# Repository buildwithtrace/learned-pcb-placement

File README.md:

# learned-pcb-placement

GNN-guided simulated annealing for PCB component placement. We train a Graph Attention Network on SA rollout data to learn which components to move and where, then use these predictions to bias the SA search. Early results show up to 9.2% HPWL reduction on KiCad designs. Dataset includes production boards up to 681 components (Antmicro Jetson Orin baseboard, HackRF One SDR).

**Paper:** [adekoya2026_gat_pcb_placement.pdf](adekoya2026_gat_pcb_placement.pdf)

## Architecture

```
KiCad .kicad_pcb
     │
     ▼
┌──────────────┐
│  S-expr Parser │ ──→ Components, Nets, Board geometry
└──────┬───────┘
       │
       ▼
┌──────────────┐     ┌──────────────┐
│  Graph Laplacian │ ──→ │ Spectral Init │ (Fiedler vectors)
│  L = D - A       │     └──────┬───────┘
└──────────────┘              │
       │                      ▼
       ▼             ┌──────────────┐
┌──────────────┐     │   SA Rollouts  │ ──→ Training data
│  GAT (2-layer)  │◀──  │  10 × short SA │     (accepted moves,
│  4-head attn    │     └──────────────┘      improvements)
│  move + quality │
└──────┬───────┘
       │
       ▼
┌──────────────────────────┐
│  GNN-Guided SA              │
│  P(component i) ∝ softmax(q_i / τ)  │
│  Δx, Δy = GNN prediction + noise    │
│  Accept via Boltzmann: e^{-ΔE/T}    │
└──────────────────────────┘
       │
       ▼
   Optimized Placement
```

## Results

Evaluated on 12 KiCad PCBs (5 to 94 components) parsed directly from `.kicad_pcb` files, sourced from open-source hardware on GitHub. Three additional production boards (207 to 681 components) are included in the dataset for GPU/TPU evaluation via Colab.

| Board | Components | Nets | SA HPWL | GNN HPWL | HPWL Δ | SA Cost | GNN Cost |
|-------|-----------|------|---------|----------|--------|---------|----------|
| stickhub | 94 | 45 | 1125.9 | **1022.1** | **-9.2%** | 1127.8 | 1757.3 |
| rp2040_debugger | 69 | 55 | 1248.8 | 1375.4 | +10.1% | 1251.1 | 1464.6 |
| motor_controller | 51 | 36 | 883.2 | 918.4 | +4.0% | 883.5 | 1116.6 |
| keyboard_rev0 | 37 | 46 | 3086.2 | 4228.8 | +37.0% | 8459.2 | 10468.6 |
| pluto_watch | 37 | 52 | 867.1 | **838.0** | **-3.4%** | 867.2 | 862.0 |
| kitchen_timer | 35 | 31 | 605.9 | 828.4 | +36.7% | 611.1 | 935.4 |
| rgb_to_hdmi | 32 | 32 | 721.9 | 776.8 | +7.6% | 723.5 | 865.7 |
| snapvcc | 26 | 8 | 136.4 | **106.9** | **-21.6%** | 136.5 | 118.2 |
| dali_stm32 | 22 | 33 | 572.5 | 721.0 | +25.9% | 572.5 | 760.6 |
| mmdvm_hotspot | 21 | 29 | 839.7 | 1033.5 | +23.1% | 840.0 | 1606.8 |
| tomu | 17 | 17 | 176.5 | **174.1** | **-1.4%** | 176.5 | 222.7 |
| m2sata | 5 | 17 | 200.1 | 410.9 | +105.3% | 200.1 | 411.7 |

**Key findings:**
- GNN achieves lower HPWL on **4 out of 12 boards** (stickhub -9.2%, snapvcc -21.6%, pluto_watch -3.4%, tomu -1.4%)
- On snapvcc (26 components), GNN also wins on **total cost** (118.2 vs 136.5), with overlap penalty of only 1.13
- Overlap remains the primary bottleneck — the quality prediction head R² is low across all boards
- GNN acceptance rates are consistently higher (80-99%) vs baseline SA (50-93%), confirming the network proposes structurally meaningful moves
- Per-board training with just 10 SA rollouts (~3-20s) — no pre-training, no large dataset

## Quick Start

```bash
pip install torch numpy matplotlib
python3 learn.py data/stickhub.kicad_pcb       # single board, default (80 epochs, 10 rollouts)
python3 graphs.py                                # generates all plots from results/
```

Or run scaled experiments on Google Colab (50 rollouts, 200 epochs, GPU/TPU): 

Requires Python 3.10+ and PyTorch with CUDA, TPU (via torch_xla), MPS (Apple Silicon), or CPU fallback.

## Data

15 KiCad PCB designs from open-source hardware, spanning hobby projects to production carrier boards:

| Board | Components | Nets | Source |
|-------|-----------|------|--------|
| jetson_orin_baseboard | 681 | 644 | [Antmicro](https://github.com/antmicro/jetson-orin-baseboard) (NVIDIA Jetson carrier) |
| hackrf_one | 437 | 319 | [Great Scott Gadgets](https://github.com/greatscottgadgets/hackrf) (production SDR) |
| artix_dc_scm | 207 | 224 | [Antmicro](https://github.com/antmicro/artix-dc-scm) (FPGA server mgmt) |
| stickhub | 94 | 45 | USB hub |
| rp2040_debugger | 69 | 55 | Raspberry Pi debug probe |
| motor_controller | 51 | 36 | H-bridge motor driver |
| keyboard_rev0 | 37 | 46 | Mechanical keyboard controller |
| pluto_watch | 37 | 52 | Casio F-91W replacement |
| kitchen_timer | 35 | 31 | MCU countdown timer |
| rgb_to_hdmi | 32 | 32 | Video signal converter |
| snapvcc | 26 | 8 | Compact power supply |
| dali_stm32 | 22 | 33 | DALI lighting interface |
| mmdvm_hotspot | 21 | 29 | Digital voice modem |
| tomu | 17 | 17 | USB-insertable ARM MCU |
| m2sata | 5 | 17 | M.2 to SATA adapter |

## Files

| File | Purpose |
|------|---------|
| `learn.py` | GAT architecture, training loop, GNN-guided SA, experiment runner |
| `placer.py` | KiCad parser, cost functions, baseline SA, spectral placement |
| `graphs.py` | Publication-quality matplotlib plots |
| `program.md` | Experiment strategy and research plan |

## Why PCB Placement is Hard

PCB placement is NP-hard. A board with N components and G grid positions has O(G^N) configurations. The optimization landscape includes wirelength, component overlap, board boundary constraints, EMC, thermal, and signal integrity — all interacting across domains.

SA has been the gold standard for 40 years because the Boltzmann acceptance criterion (`P = e^{-ΔE/T}`) allows escaping local minima. But SA relies on random move proposals. Our insight: a GNN trained on short SA rollouts can learn which components to move and in which direction, replacing random exploration with informed proposals.

## Related Work

All serious placement research targets VLSI/ASIC. PCB placement is wide open.

| Paper | Venue | Contribution |
|-------|-------|-------------|
| [AlphaChip](https://www.nature.com/articles/s41586-021-03544-w) (Mirhoseini et al.) | Nature 2021 | RL for ASIC floorplanning, deployed in Google TPUs |
| [DREAMPlace](https://ieeexplore.ieee.org/document/9122053) (Lin et al.) | DAC 2019 | Placement as neural network training, 40x GPU speedup |
| [TransPlace](https://arxiv.org/abs/2501.05667) (Cheng et al.) | KDD 2025 | Transferable GNN global placement |
| [ChipDiffusion](https://arxiv.org/abs/2407.12282) (Vint et al.) | ICML 2025 | Diffusion for zero-shot chip placement |
| [DiffPlace](https://arxiv.org/abs/2510.15897) (Liu et al.) | 2025 | Conditional diffusion for VLSI with constraints |
| [Cypress](https://www.csl.cornell.edu/~zhiruz/pdfs/cypress-ispd2025.pdf) (Lu et al.) | ISPD 2025 | **VLSI-inspired PCB placement with GPU acceleration** (Best Paper) |
| [C3PO](https://research.nvidia.com/labs/electronic-design-automation/) (Lu et al.) | ASP-DAC 2026 | Commercial-quality global placement |
| [Netlistify](https://research.nvidia.com/labs/electronic-design-automation/) (Huang et al.) | MLCAD 2025 | Schematics to netlists with deep learning (Best Artifact) |
| [PCB-Bench](https://openreview.net/forum?id=Q5QLu7XTWx) | ICLR 2026 | First LLM benchmark for PCB tasks |
| [Component Centric Placement](https://arxiv.org/abs/2602.23540) | arXiv 2026 | PCB-specific graph representations |
| [GNN for PCB Schematics](https://arxiv.org/abs/2502.14600) | 2025 | Auto-adding decoupling caps via graph prediction |

## Current Scope

The cost function today optimizes three things:

- **HPWL (wirelength)** — total half-perimeter wirelength across all nets. Shorter wires mean easier routing, lower resistance, and less parasitic inductance.
- **Overlap penalty** — components must not physically intersect. Penalized quadratically.
- **Boundary penalty** — all components must stay within the board outline.

These are the standard baseline metrics for placement research (VLSI uses the same starting point). The system does **not** yet model:

- **Decoupling capacitor proximity** — bypass caps must sit within a few mm of their IC's power pins. The netlist already encodes this relationship (cap and IC share a power net), so the GNN graph contains the signal — it just isn't weighted yet.
- **Functional group clustering** — power regulation, analog front-end, digital core, and I/O should form coherent groups. Today the placer treats all components equally.
- **EMI/EMC separation** — noisy switching regulators should be far from sensitive analog inputs. High-speed clock traces should be short and shielded. Not modeled.
- **Signal integrity** — matched-length differential pairs, controlled impedance, return path continuity. Not modeled.
- **Thermal constraints** — power components need spacing and copper pour area for heat dissipation. Not modeled.
- **Mechanical constraints** — keep-out zones, mounting holes, connector edge placement. Not modeled.

The roadmap is to add these as weighted terms in the cost function (e.g., `cost = HPWL + overlap + decoupling_distance + group_separation + EMI_penalty`) and encode constraint types as edge features in the GNN graph so the network learns that some connections (power net between cap and IC) matter more than others (signal net between distant connectors).

## What's Next

The GNN learns wirelength optimization but underfits on quality prediction (R² ≈ 0.001–0.079), which is why overlap isn't resolved. The local runs used only 10 rollouts and 80 epochs — not enough signal. The path forward:

1. **Scale training on Colab** — 50 rollouts, 200 epochs on GPU/TPU. 5x more data should address underfitting on the quality head.
2. **Overlap-aware loss** — penalize overlap in the GNN training objective, not just in the SA cost function.
3. **Cross-board pre-training** — train a single model on all 12 boards jointly, evaluate transfer to unseen designs.
4. **Constraint-aware cost function** — add decoupling cap proximity, functional group clustering, and EMI separation penalties. Encode net types (power, signal, clock) as edge features so the GNN learns constraint priorities.
5. **Longer rollouts** — current rollouts are short (T: 10→2). Longer annealing gives the GNN better examples of overlap resolution.
6. **Diffusion hybrid** — use a diffusion model for initial placement, then GNN-guided SA for refinement.

## Authors

- [Ayomide Adekoya](https://github.com/elcruzo)
- [Jeff Allo](https://github.com/jeff4444)
- [Olu Afolabi](https://github.com/oluuafolabii)

Built by [Trace](https://buildwithtrace.com) — an AI-native PCB design tool.
Also mirrored at [buildwithtrace/learned-pcb-placement](https://github.com/buildwithtrace/learned-pcb-placement).

## License

MIT

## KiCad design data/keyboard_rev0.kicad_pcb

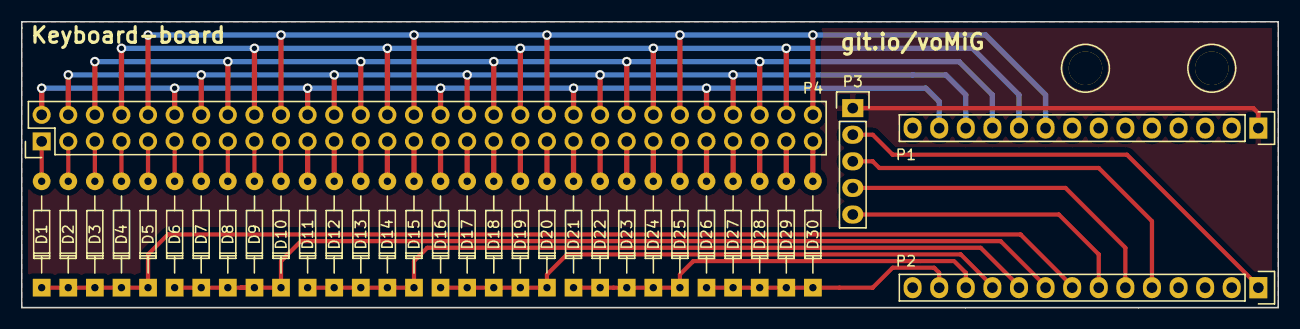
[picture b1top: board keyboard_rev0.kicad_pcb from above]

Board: 2 copper layers, 120.0 x 27.3 mm, 34 parts (0 on the bottom side), 46 nets.

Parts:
D1, D2, D3, D4, D5, D6, D7, D8, D9, D10, D11, D12, D13, D14, D15, D16, D17, D18, D19, D20, D21, D22, D23, D24, D25, D26, D27, D28, D29, D30: 1n4148; Diode_DO-35_SOD27_Horizontal_RM10
P1, P2: CONN_01X14; Socket_Strip_Straight_1x14
P3: CONN_01X05; Pin_Header_Straight_1x05
P4: CONN_02X30; Pin_Header_Straight_2x30

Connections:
+5V: P2.1, P3.2
COL0: D1.1, D2.1, D3.1, D4.1, D5.1, P2.8
COL1: D6.1, D7.1, D8.1, D9.1, D10.1, P2.9
COL2: D11.1, D12.1, D13.1, D14.1, D15.1, P2.10
COL3: D16.1, D17.1, D18.1, D19.1, D20.1, P2.11
COL4: D21.1, D22.1, D23.1, D24.1, D25.1, P2.12
COL5: D26.1, D27.1, D28.1, D29.1, D30.1, P2.13
GND: P1.1, P3.1
unnamed: D1.2, P4.1
unnamed: D2.2, P4.3
unnamed: D3.2, P4.5
unnamed: D4.2, P4.7
unnamed: D5.2, P4.9
unnamed: D6.2, P4.11
unnamed: D7.2, P4.13
unnamed: D8.2, P4.15
unnamed: D9.2, P4.17
unnamed: D10.2, P4.19
unnamed: D11.2, P4.21
unnamed: D12.2, P4.23
unnamed: D13.2, P4.25
unnamed: D14.2, P4.27
unnamed: D15.2, P4.29
unnamed: D16.2, P4.31
unnamed: D17.2, P4.33
unnamed: D18.2, P4.35
unnamed: D19.2, P4.37
unnamed: D20.2, P4.39
unnamed: D21.2, P4.41
unnamed: D22.2, P4.43
unnamed: D23.2, P4.45
unnamed: D24.2, P4.47
unnamed: D25.2, P4.49
unnamed: D26.2, P4.51
unnamed: D27.2, P4.53
unnamed: D28.2, P4.55
unnamed: D29.2, P4.57
unnamed: D30.2, P4.59
ROW0: P1.13, P4.2, P4.12, P4.22, P4.32, P4.42, P4.52
ROW1: P1.12, P4.4, P4.14, P4.24, P4.34, P4.44, P4.54
ROW2: P1.11, P4.6, P4.16, P4.26, P4.36, P4.46, P4.56
ROW3: P1.10, P4.8, P4.18, P4.28, P4.38, P4.48, P4.58
ROW4: P1.9, P4.10, P4.20, P4.30, P4.40, P4.50, P4.60
SW: P2.7, P3.5
VRx: P2.5, P3.3
VRy: P2.6, P3.4

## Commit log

2026-03-09 GNN-guided SA for PCB placement: initial results
    - GAT (2-layer, 4-head) trained on SA rollouts to predict component moves
    - Evaluated on stickhub (94 components) and rp2040_debugger (69 components)
    - GNN achieves lowest HPWL: -9.2% vs baseline SA on stickhub
    - IEEE-format paper, matplotlib plots, full reproducible pipeline
    - Parses real .kicad_pcb files via custom s-expression parser
2026-03-09 Scale to 12 boards from open-source KiCad repos on GitHub
2026-03-09 scale up for Colab: 50 rollouts, 200 epochs, GPU/TPU support
    - learn.py: auto-detect CUDA/TPU/MPS/CPU, configurable epochs+rollouts
    - colab.ipynb: scaled hyperparams (50 rollouts, 200 epochs), TPU install,
    Google Drive save, device diagnostics
    - README: add author profiles (elcruzo, jeff4444, oluuafolabi), org mirror
    link, TPU mention, updated "What's Next" with underfitting analysis
    - program.md: expanded phase 3 analysis (12 boards, underfitting diagnosis),
2026-03-09 fix overlapping x-axis labels on cross-board chart
    - rotate labels 45 degrees with right-aligned text
    - widen figure dynamically based on board count
    - increase bar width for better readability
2026-03-09 remove redundant "real" from KiCad PCB references, set up dual-push
    - "real KiCad PCBs" -> "KiCad PCBs" in README and program.md
    - origin now pushes to both elcruzo and buildwithtrace repos
2026-03-09 add production boards, fix email, verify data, fix links
    - add 3 production-grade PCBs: Antmicro Jetson Orin baseboard (681
    components), HackRF One SDR (437), Antmicro Artix DC-SCM (207)
    - fix email: ayo@buildwithtrace.com
    - fix Olu's GitHub: oluafolabi (not oluuafolabi)
    - fix bare arxiv.org links in README related work table
    - fix Cypress link to actual PDF instead of lab page
2026-03-09 fix Olu's GitHub username to oluuafolabii
2026-03-09 fix Olu's GitHub username in colab notebook
2026-03-09 fix colab: torch/numpy already preinstalled, only install matplotlib
2026-03-09 restore commented TPU install option in colab
2026-03-09 colab: TPU by default, no redundant pip installs
2026-03-09 colab: nothing is optional, clean up all hedging
2026-03-09 add current scope, constraint gap, and roadmap for production constraints
    README: new "Current Scope" section documenting what the cost function
    covers (HPWL, overlap, boundary) and what it doesn't yet (decoupling cap
    proximity, EMI/EMC, signal integrity, thermal, mechanical). Expanded
    "What's Next" with constraint-aware cost function milestone.
    Paper: new "Constraint Gap" subsection in Discussion detailing each
    missing constraint and how the GNN graph representation extends to
2026-03-09 colab: fix ModuleNotFoundError after kernel restart
    Each cell now does os.chdir('/content/learned-pcb-placement') and
    sys.path.insert(0, '.') so imports work regardless of whether %cd
    from cell 1 persisted (it doesn't survive kernel restarts).
2026-03-09 colab: handle already-cloned repo gracefully
    Cell 1 now checks if the repo exists — pulls latest if yes, clones if no.
    No more fatal error on re-run.
